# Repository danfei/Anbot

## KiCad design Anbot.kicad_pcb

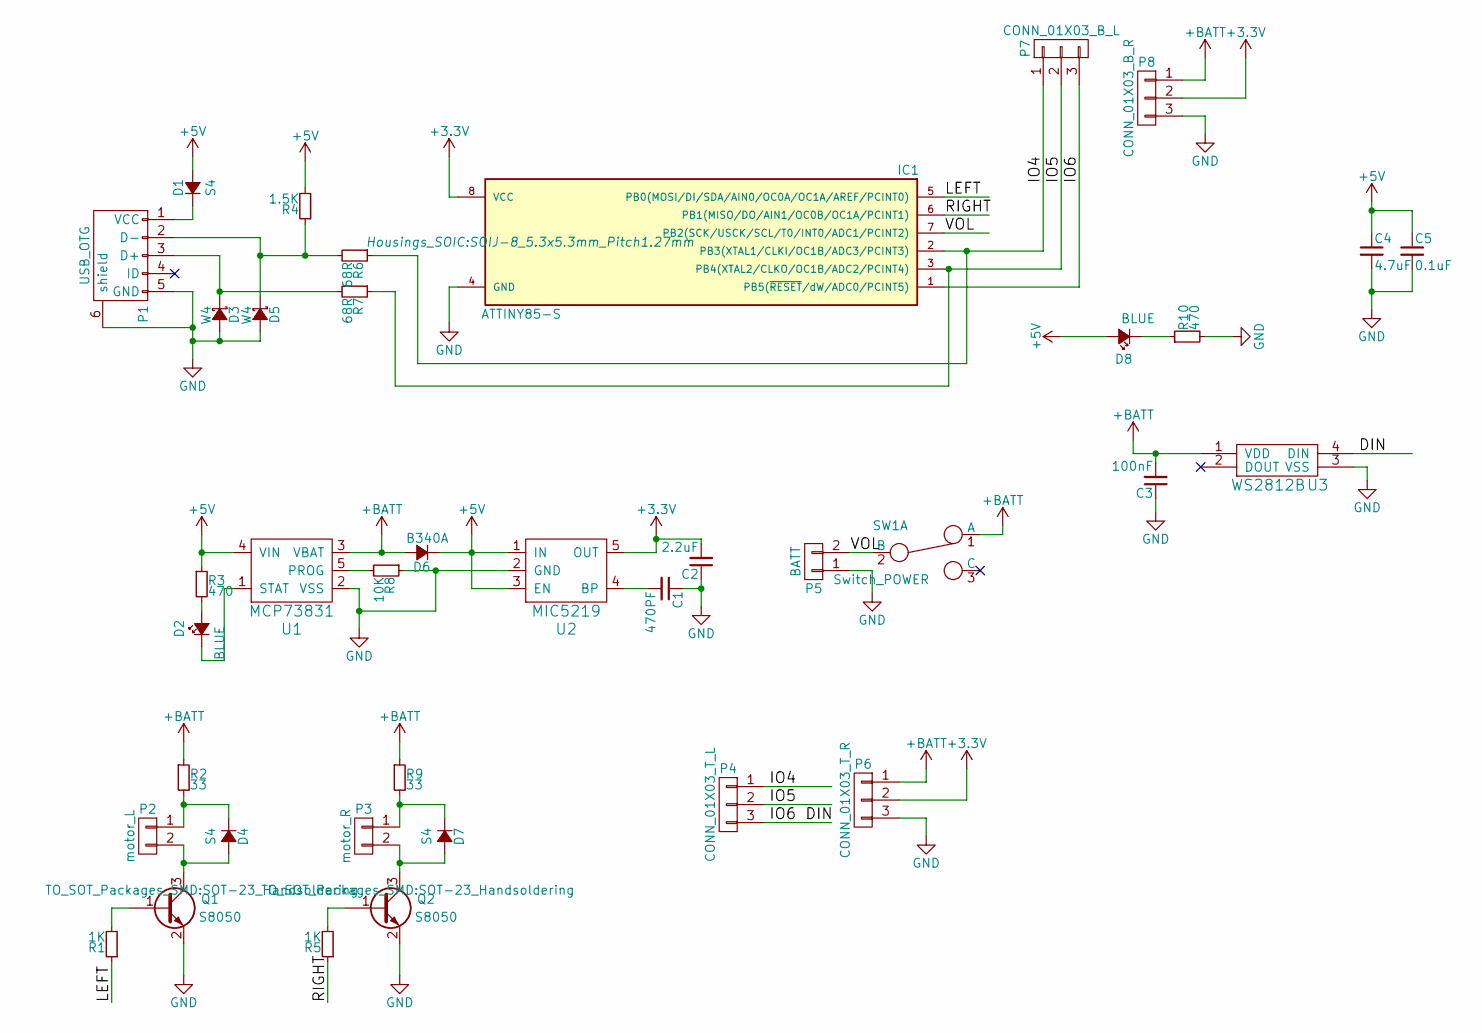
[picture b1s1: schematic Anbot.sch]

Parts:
C1: 470PF; C_0603_HandSoldering
C2: 2.2uF; C_0603_HandSoldering
C3: 100nF; C_0603_HandSoldering
C4: 4.7uF; C_0603_HandSoldering
C5: 0.1uF; C_0603_HandSoldering
D1, D4, D7: S4; SOD-123
D2, D8: BLUE; LED_0603
D3, D5: W4; SOD-123
D6: B340A
IC1: ATTINY85-S; SOIJ-8_5.3x5.3mm_Pitch1.27mm
P1: USB_OTG; USB_Micro-B
P2: motor_L; CONN_motor
P3: motor_R; CONN_motor
P4: CONN_01X03_T_L; Pin_Header_Straight_1x03
P5: BATT; CR2477
P6: CONN_01X03_T_R; Pin_Header_Straight_1x03
P7: CONN_01X03_B_L; Pin_Header_Straight_1x03
P8: CONN_01X03_B_R; Pin_Header_Straight_1x03
Q1, Q2: S8050; SOT-23_Handsoldering
R1, R5: 1K; R_0603_HandSoldering
R2, R9: 33; R_0603_HandSoldering
R3, R10: 470; R_0603_HandSoldering
R4: 1.5K; R_0603_HandSoldering
R6, R7: 68R; R_0603_HandSoldering
R8: 10K; R_0603_HandSoldering
SW1: Switch_POWER; SW_SPDT_PCM12
U1: MCP73831; SOT-23-5
U2: MIC5219; SOT-23-5
U3: WS2812B; LED_WS2812B-PLCC4

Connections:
+3V3: C2.2, IC1.8 (VCC), P6.2, P8.2, U2.5 (OUT)
+5V: C4.1, C5.1, D1.2 (A), D6.1 (K), D8.2 (A), R3.1, R4.2, U1.4 (VIN), U2.1 (IN), U2.3 (EN); also elsewhere on the board
+BATT: C3.2, D6.2 (A), P6.1, P8.1, R2.1, R9.1, SW1.1 (A), U1.3 (VBAT), U3.1 (VDD)
/DIN: IC1.1 (PB5(~RESET~/dW/ADC0/PCINT5)), P4.3, P7.3, U3.4 (DIN)
/IO4: IC1.2 (PB3(XTAL1/CLKI/OC1B/ADC3/PCINT3)), P4.1, P7.1, R6.1
/IO5: IC1.3 (PB4(XTAL2/CLKO/OC1B/ADC2/PCINT4)), P4.2, P7.2, R7.1
/LEFT: IC1.5 (PB0(MOSI/DI/SDA/AIN0/OC0A/OC1A/AREF/PCI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), R1.1
/RIGHT: IC1.6 (PB1(MISO/DO/AIN1/OC0B/OC1A/PCINT1)), R5.1
/VOL: IC1.7 (PB2(SCK/USCK/SCL/T0/INT0/ADC1/PCINT2)), P5.2, SW1.2 (B)
GND: C1.1, C2.1, C3.1, C4.2, C5.2, D3.2 (A), D5.2 (A), IC1.4 (GND), P1.5 (GND), P1.6 (shield), P5.1, P6.3, P8.3, Q1.2 (E), Q2.2 (E), R8.1, R10.2, U1.2 (VSS), U2.2 (GND), U3.3 (VSS); also elsewhere on the board
unnamed: C1.2, U2.4 (BP)
unnamed: D1.1 (K), P1.1 (VCC)
unnamed: D2.1 (K), U1.1 (STAT)
unnamed: D2.2 (A), R3.2
unnamed: D3.1 (K), P1.3 (D+), R7.2
unnamed: D4.1 (K), P2.1, R2.2
unnamed: D4.2 (A), P2.2, Q1.3 (C)
unnamed: D5.1 (K), P1.2 (D-), R4.1, R6.2
unnamed: D7.1 (K), P3.1, R9.2
unnamed: D7.2 (A), P3.2, Q2.3 (C)
unnamed: D8.1 (K), R10.1
unnamed: Q1.1 (B), R1.2
unnamed: Q2.1 (B), R5.2
unnamed: R8.2, U1.5 (PROG)

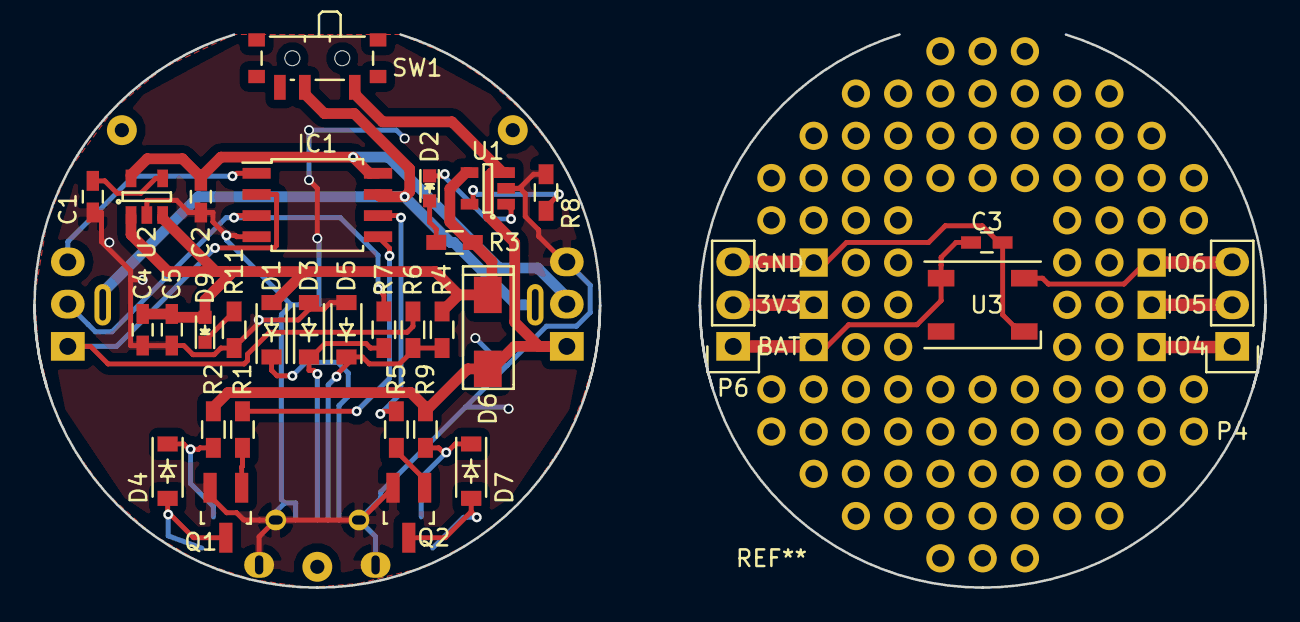
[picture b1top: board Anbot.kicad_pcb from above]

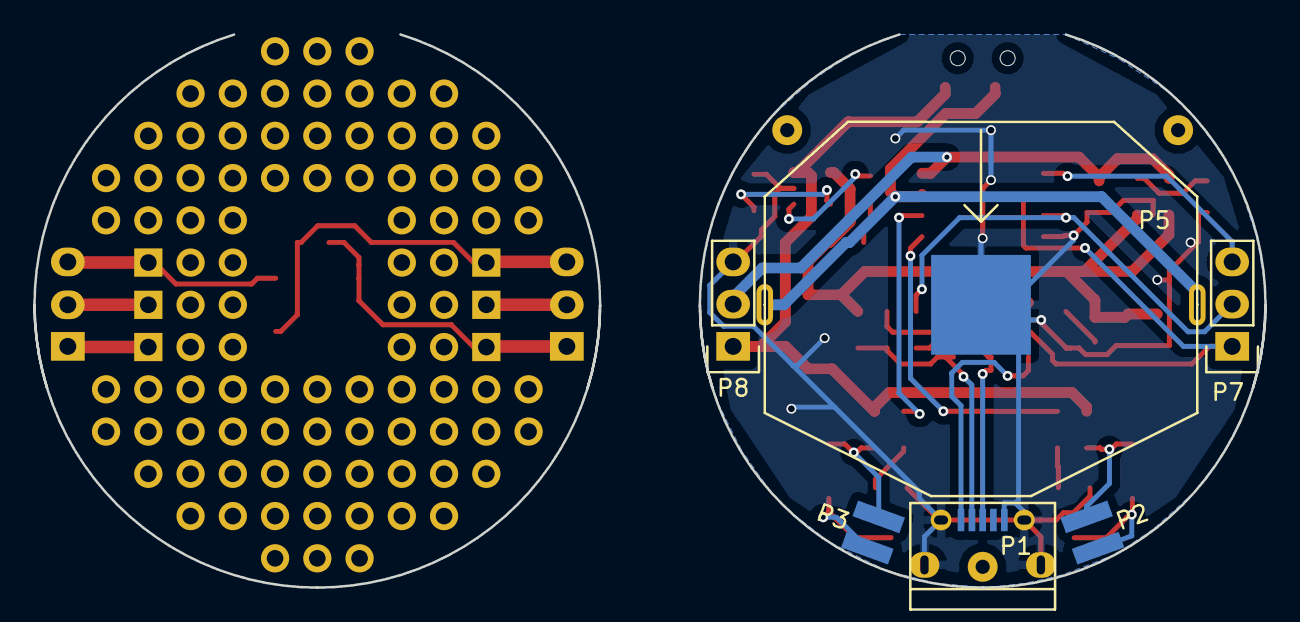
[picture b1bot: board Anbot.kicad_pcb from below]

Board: 2 copper layers, 74.0 x 33.2 mm, 41 parts (9 on the bottom side), 24 nets.

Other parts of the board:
D9: BLUE; LED_0603
R11: 470; R_0603_HandSoldering
foot1, foot2, foot3: foot; botfoot

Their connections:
+5V: D9.2; also elsewhere on the board
GND: R11.2; also elsewhere on the board
unnamed: D9.1, R11.1

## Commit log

2016-12-23 Alpha version
